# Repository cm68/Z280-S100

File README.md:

# Z280 S-100 CPU Card

A 16-bit **Zilog Z280** CPU card for the **IEEE-696 S-100** backplane. All the
glue logic lives in two **Atmel ATF1508AS** CPLDs, and the entire schematic +
PCB are Python-generated (`gen_kicad.py`, `gen_pcb.py`).

## Key characteristics

| | |
|---|---|
| CPU | Zilog Z280, 16-bit, Z-BUS @ **12 MHz** |
| Bus | IEEE-696 S-100, 100-pin edge connector |
| Glue logic | 2× Atmel ATF1508AS (128 macrocells each) |
| RAM | **2 MB** SRAM — 4× IS61C5128AS-25 (512K×8, 25 ns), word-addressed as 1M×16 |
| Boot ROM | **64 KB** EEPROM — 2× AT28C256 (32K×8) |
| Console | RS-232 via MAX232, 2×5 IDC header (J7) |
| Data-bus drive | 74F245 — meets the IEEE-696 24 mA sink spec |

The board is a **bus master** by default: it drives address, status, control and
data onto the backplane. The CPLDs split the work cleanly:

- **Control CPLD** (`U4`, `z280-s100-ctl.pld`) — "the decider". Arbitration, the
  master-bridge state machine, local-memory control, and the pre-qualified
  steering terms (`MST_RD/MST_WR/SLV_RD/SLV_WR`, `XFR16`, `SPLIT`, `SLAVE`).
- **Data CPLD** (`U5`, `z280-s100-ad.pld`) — "everything that moves bits". The
  AD0-15 byte mux to the S-100 DO/DI lanes, the burst address counter, and the
  byte lane.

Address decode is external: a 74F138 (SRAM window) + two 74F521 comparators
(flash window, slave window). The A3–A15 address lines are latched out through
two 74F573s, and the 16-bit data bus runs through two 74F245 transceivers.

## Memory map (24-bit address space)

| Range | Size | Decode | Device |
|---|---|---|---|
| `000000`–`1FFFFF` | 2 MB | 74F138 (`SRAM_WIN`) / 74F521 (`SLAVE_WIN`) | SRAM — board + temporary-master access |
| `F00000`–`F0FFFF` | 64 KB | 74F521, A23:A16 = `F0` | Boot EEPROM |

The boot EEPROM pair is word-addressed (flash A_n = byte A_{n+1}), so the two
parts span 64 KB. They are *not* socket-interchangeable with 27C256s (pin 27 is
`WE#` here, not A14).

## Local-memory DMA (temporary-master access)

Another S-100 master can take the bus and read/write this card's local SRAM
directly — DMA-style, without the Z280:

1. The temporary master (TMA) asserts **HOLD**; the control CPLD forwards the
   request to the Z280 (`Z_BUSREQ`) and waits for `Z_BUSACK`.
2. With `Z_BUSACK` low the board is a **slave**
   (`SLAVE = !Z_BUSACK # SLAVE_ONLY`): the address/status/control 74F245s
   reverse direction, the data 74F245s float (`S100_DODSB`), and the 74F573
   address latches float their outputs.
3. The TMA reaches this card's RAM through the **slave window** — a
   74F521 comparator (`SLAVE_WIN`, hardwired to `000000`–`1FFFFF`) that maps
   the TMA's address space onto the local SRAM.

The **SLAVE_ONLY** strap (J11) forces this state permanently, turning the card
into a plain memory-only card for bring-up and debug.

## Burst mode

The Z280's memory burst mode (consecutive accesses without re-presenting the
address) is handled in the data CPLD:

- a **2-bit burst address counter** (A1/A2) increments during a burst;
- the **byte lane** (A0) is derived from the low-address bit and the 16→8
  **SPLIT** flag, so byte and word cycles share one data path;
- **16-bit transfers** are detected from WORD and the S-100 **SIXTN**
  (16-bit-acknowledge) line: `SPLIT16 = WORD & !SIXTN`.

`SIXTN` is open-collector (wired-OR) and pulled up via R4, like the ready lines.

## Clock options

Two 24 MHz time-base footprints are laid out; populate exactly **one**:

- **Y1** — parallel-resonant crystal (HC49) across `XTALI`/`XTALO`, or
- **Y2** — a DIP-can oscillator (DIP-8 or DIP-14) driving `XTALI`.

The Z280 auto-detects the source: a crystal enables the on-chip oscillator, while
an external clock into `XTALI` bypasses it (leave `XTALO` open). There is no
strap for this. Either way the CPU clock is half the XTAL1 frequency, so
**24 MHz → 12 MHz processor clock**.

## Configuration jumpers

### J10 — BTI register straps (3×8 header)

The Z280 samples AD0-7 on the rising edge of reset to load its **Bus Timing &
Initialization (BTI)** register — the wait-state field, clock divider,
bootstrap and multiprocessor bits. J10 is a 3×8 header, one row per bit: the
centre pin selects +5V (logic 1) or GND (logic 0); a 74HCT244 (U21) drives the
value onto AD0-7 for the whole reset window.

**Default = `0b10001110`** (AD7…AD0): direct clock, no bootstrap, no
multiprocessor, **3 wait states**, bus clock = CPU clock.

### J11 — SLAVE_ONLY

2-pin header. **Open (default)** = normal bus master. **Jumper to +5V** =
permanent slave (memory-only card). R3 (1 kΩ) holds the line low when open.

### SLAVE_WIN — temporary-master window

A 74F521 comparator hardwired to `000000`–`1FFFFF` (the same 2 MB window as
SRAM) selects where a temporary master sees this card's SRAM. Not user-
configurable on this rev.

### FLASH_WE — boot-ROM write protection

The 28C256 `WE#` line is normally driven by the control CPLD (in-system EEPROM
programming). Strap it to +5V to hard-write-protect the boot ROM.

## Repository layout

| Path | Purpose |
|---|---|
| `gen_kicad.py` | Generates the schematic (`.kicad_sch`, `.kicad_sym`, `NOTES.md`) |
| `gen_pcb.py` | Generates the board (`.kicad_pcb`) — components, nets, power planes |
| `sync_pcb.py` | Reads hand-tweaked PCB placement back into `gen_pcb.py` |
| `z280-s100-ctl.pld` | Control CPLD (U4) logic — arbitration, FSM, memory control |
| `z280-s100-ad.pld` | Data CPLD (U5) logic — byte mux, burst counter, byte lane |
| `z280-s100-*.jed` | Compiled CPLD fuse maps (fit with WinCUPL + ProChip, flashed over JTAG) |

CPLDs are flashed over the JTAG header (TDI/TMS/TCK/TDO on pins 14/23/62/71).

## License

[CERN Open Hardware Licence Version 2 - Permissive](LICENSE) (CERN-OHL-P-2.0).
Fork, modify and build it freely — just don't claim you designed it: keep the
attribution.

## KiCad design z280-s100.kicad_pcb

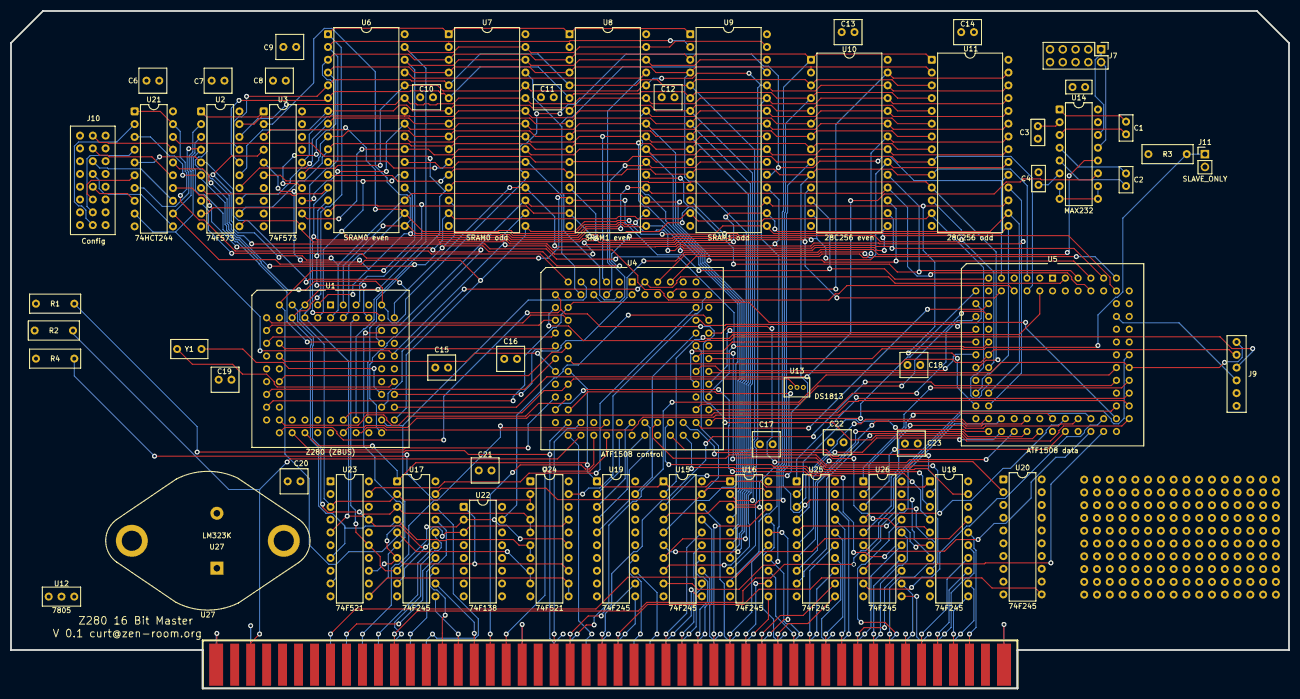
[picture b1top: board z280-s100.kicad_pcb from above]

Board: 4 copper layers, 254.0 x 134.6 mm, 60 parts (0 on the bottom side), 202 nets.

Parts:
C1, C2, C3, C4, C5: 0.1uF; C_Disc_D5.0mm_W2.5mm_P2.50mm
C6, C7, C8, C9, C10, C11, C12, C13, C14, C15, C16, C17, C18, C19, C20, C21, C22, C23: 0.1uF; CAP-2
J7: Serial (2x5); PinHeader_2x05_P2.54mm_Vertical
J9: JTAG; HDR-6
J10: Config; HDR-3x8
J11: SLAVE_ONLY; PinHeader_1x02_P2.54mm_Vertical
R1: 1k pRDY; HDR-2
R2: 1k XRDY; HDR-2
R3: 1k SLAVE_ONLY; HDR-2
R4: 1k SIXTN; HDR-2
U1: Z280 (ZBUS); PLCC-68_THT-Socket
U2, U3: 74F573; DIP-20_W7.62mm
U4: ATF1508 control; PLCC-84_THT-Socket
U5: ATF1508 data; PLCC-84_THT-Socket
U6: SRAM0 even; DIP-32_W15.24mm
U7: SRAM0 odd; DIP-32_W15.24mm
U8: SRAM1 even; DIP-32_W15.24mm
U9: SRAM1 odd; DIP-32_W15.24mm
U10: 28C256 even; DIP-28_W15.24mm
U11: 28C256 odd; DIP-28_W15.24mm
U12: 7805; HDR-3
U13: DS1813; HDR-3
U14: MAX232; DIP-16_W7.62mm
U15, U16, U17, U18, U19, U20, U25, U26: 74F245; DIP-20_W7.62mm
U21: 74HCT244; DIP-20_W7.62mm
U22: 74F138; DIP-16_W7.62mm
U23, U24: 74F521; DIP-20_W7.62mm
U27: LM323K; TO-3
V 0.1 curt@zen-room.org: Z280 16 Bit Master; S100_MALE
Y1: 24 MHz crystal; HDR-2

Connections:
+5V: C5.1, C6.1, C7.1, C8.1, C9.1, C10.1, C11.1, C12.1, C13.1, C14.1, C15.1, C16.1, C17.1, C18.1, C19.1, C20.1, C21.1, C22.1, C23.1, J9.6, J10.1, J10.4, J10.7, J10.10, J10.13, J10.16, J10.19, J10.22, J11.2, R1.1, R2.1, R4.1, U1.18, U1.19, U1.34, U2.20, U3.20, U4.1, U4.2, U4.3, U4.13, U4.26, U4.38, U4.43, U4.53, U4.66, U4.78, U4.84, U5.1, U5.2, U5.3, U5.13, U5.26, U5.38, U5.43, U5.53, U5.66, U5.78, U5.84, U6.32, U7.32, U8.32, U9.32, U10.28, U11.28, U12.3, U13.3, U14.16, U15.20, U16.20, U17.20, U18.20, U19.20, U20.1, U20.20, U21.20, U22.6, U22.16, U23.12, U23.14, U23.16, U23.18, U23.20, U24.20, U25.20, U26.20, U27.2
+8V: U12.1, U27.1, V 0.1 curt@zen-room.org.1, V 0.1 curt@zen-room.org.51
A0: U5.4, U15.2
A1: U5.5, U6.12, U7.12, U8.12, U9.12, U10.10, U11.10, U15.3
A2: U5.6, U6.11, U7.11, U8.11, U9.11, U10.9, U11.9, U15.4
A3: U2.12, U6.10, U7.10, U8.10, U9.10, U10.8, U11.8, U15.5
A4: U2.13, U6.9, U7.9, U8.9, U9.9, U10.7, U11.7, U15.6
A5: U2.14, U6.8, U7.8, U8.8, U9.8, U10.6, U11.6, U15.7
A6: U2.15, U6.7, U7.7, U8.7, U9.7, U10.5, U11.5, U15.8
A7: U2.16, U6.6, U7.6, U8.6, U9.6, U10.4, U11.4, U15.9
A8: U2.17, U6.5, U7.5, U8.5, U9.5, U10.3, U11.3, U16.2
A9: U2.18, U6.27, U7.27, U8.27, U9.27, U10.25, U11.25, U16.3
A10: U2.19, U6.26, U7.26, U8.26, U9.26, U10.24, U11.24, U16.4
A11: U3.12, U6.23, U7.23, U8.23, U9.23, U10.21, U11.21, U16.5
A12: U3.13, U6.25, U7.25, U8.25, U9.25, U10.23, U11.23, U16.6
A13: U3.14, U6.4, U7.4, U8.4, U9.4, U10.2, U11.2, U16.7
A14: U3.15, U6.28, U7.28, U8.28, U9.28, U10.26, U11.26, U16.8
A15: U3.16, U6.3, U7.3, U8.3, U9.3, U10.1, U11.1, U16.9
A16: U1.5, U6.31, U7.31, U8.31, U9.31, U17.2, U23.3, U24.2, U24.3
A17: U1.6, U6.2, U7.2, U8.2, U9.2, U17.3, U23.5, U24.4, U24.5
A18: U1.8, U6.1, U7.1, U8.1, U9.1, U17.4, U23.7, U24.6, U24.7
A19: U1.9, U6.30, U7.30, U8.30, U9.30, U17.5, U23.9, U24.8, U24.9
A20: U1.45, U4.9, U17.6, U23.11, U24.11, U24.12
A21: U1.59, U17.7, U22.1, U23.13, U24.13
A22: U1.66, U17.8, U22.2, U23.15, U24.15
A23: U1.7, U17.9, U22.3, U23.17, U24.17
AD0: U1.40, U5.24, U7.13, U9.13, U11.11, U21.18
AD1: U1.42, U5.25, U7.14, U9.14, U11.12, U21.16
AD2: U1.43, U5.27, U7.15, U9.15, U11.13, U21.14
AD3: U1.44, U2.2, U5.28, U7.17, U9.17, U11.15, U21.12
AD4: U1.54, U2.3, U5.29, U7.18, U9.18, U11.16, U21.9
AD5: U1.57, U2.4, U5.30, U7.19, U9.19, U11.17, U21.7
AD6: U1.60, U2.5, U5.31, U7.20, U9.20, U11.18, U21.5
AD7: U1.61, U2.6, U5.9, U7.21, U9.21, U11.19, U21.3
AD8: U1.62, U2.7, U5.10, U6.13, U8.13, U10.11
AD9: U1.64, U2.8, U5.11, U6.14, U8.14, U10.12
AD10: U1.65, U2.9, U5.75, U6.15, U8.15, U10.13
AD11: U1.67, U3.2, U5.76, U6.17, U8.17, U10.15
AD12: U1.68, U3.3, U5.77, U6.18, U8.18, U10.16
AD13: U1.2, U3.4, U5.79, U6.19, U8.19, U10.17
AD14: U1.3, U3.5, U5.80, U6.20, U8.20, U10.18
AD15: U1.4, U3.6, U5.81, U6.21, U8.21, U10.19
BTI_AD0: J10.2, U21.2
BTI_AD1: J10.5, U21.4
BTI_AD2: J10.8, U21.6
BTI_AD3: J10.11, U21.8
BTI_AD4: J10.14, U21.11
BTI_AD5: J10.17, U21.13
BTI_AD6: J10.20, U21.15
BTI_AD7: J10.23, U21.17
CFG_OE: U4.11, U21.1, U21.19
CPLD_DI0: U5.44, U26.2
CPLD_DI1: U5.45, U26.3
CPLD_DI2: U5.46, U26.4
CPLD_DI3: U5.48, U26.5
CPLD_DI4: U5.49, U26.6
CPLD_DI5: U5.50, U26.7
CPLD_DI6: U5.51, U26.8
CPLD_DI7: U5.52, U26.9
CPLD_DO0: U5.33, U25.2
CPLD_DO1: U5.34, U25.3
CPLD_DO2: U5.35, U25.4
CPLD_DO3: U5.36, U25.5
CPLD_DO4: U5.37, U25.6
CPLD_DO5: U5.39, U25.7
CPLD_DO6: U5.40, U25.8
CPLD_DO7: U5.41, U25.9
CPLD_pDBIN: U4.45, U19.4
CPLD_pHLDA: U4.48, U20.2
CPLD_pSTVAL: U4.44, U19.3
CPLD_pSYNC: U4.41, U19.2
CPLD_pWR: U4.46, U19.5
CPLD_sHLTA: U4.31, U18.7
CPLD_sINP: U4.51, U18.4
CPLD_sINTA: U4.30, U18.6
CPLD_sMEMR: U4.49, U18.2
CPLD_sOUT: U4.52, U18.5
CPLD_sWO: U4.50, U18.3
CPLD_sXTRQ: U4.65, U18.8
DI_DIR: U5.60, U26.1
DO_DIR: U5.58, U25.1
FLASH_CE: U4.81, U10.20, U11.20
FLASH_OE: U4.79, U10.22, U11.22
FLASH_WE: U4.80, U10.27, U11.27
FLASH_WIN: U4.73, U23.19
GND: C3.2, C4.2, C5.2, C6.2, C7.2, C8.2, C9.2, C10.2, C11.2, C12.2, C13.2, C14.2, C15.2, C16.2, C17.2, C18.2, C19.2, C20.2, C21.2, C22.2, C23.2, J7.3, J7.4, J7.5, J7.6, J7.7, J7.8, J7.9, J7.10, J9.5, J10.3, J10.6, J10.9, J10.12, J10.15, J10.18, J10.21, J10.24, R3.1, U1.1, U1.35, U1.51, U1.53, U2.10, U3.7, U3.8, U3.9, U3.10, U4.7, U4.19, U4.32, U4.42, U4.47, U4.59, U4.72, U4.82, U5.7, U5.19, U5.32, U5.42, U5.47, U5.59, U5.72, U5.82, U6.16, U7.16, U8.16, U9.16, U10.14, U11.14, U12.2, U13.1, U14.15, U15.10, U16.10, U17.10, U18.10, U19.10, U20.3, U20.4, U20.5, U20.6, U20.7, U20.8, U20.9, U20.10, U20.19, U21.10, U22.4, U22.5, U22.8, U23.1, U23.2, U23.4, U23.6, U23.8, U23.10, U24.1, U24.10, U24.14, U24.16, U24.18, U25.10, U25.19, U26.10, U26.19, U27.3, V 0.1 curt@zen-room.org.20, V 0.1 curt@zen-room.org.50, V 0.1 curt@zen-room.org.53, V 0.1 curt@zen-room.org.70, V 0.1 curt@zen-room.org.100
JTAG_CHAIN: U4.71, U5.14
JTAG_TCK: J9.1, U4.62, U5.62
JTAG_TDI: J9.3, U4.14
JTAG_TDO: J9.4, U5.71
JTAG_TMS: J9.2, U4.23, U5.23
LA0: U4.63, U5.22
LATCH_LE: U2.11, U3.11, U5.8
MAX_C1M: C1.2, U14.3
MAX_C1P: C1.1, U14.1
MAX_C2M: C2.2, U14.5
MAX_C2P: C2.1, U14.4
MAX_RS232_RX: J7.2, U14.13
MAX_RS232_TX: J7.1, U14.14
MAX_VM: C4.1, U14.6
MAX_VP: C3.1, U14.2
MEM_CE0: U4.10, U6.22, U7.22
MEM_CE1: U4.8, U8.22, U9.22
MEM_OE: U4.5, U6.24, U7.24, U8.24, U9.24
MEM_WE_H: U4.4, U7.29, U9.29
MEM_WE_L: U4.6, U6.29, U8.29
MST_RD: U4.54, U5.12
MST_WR: U4.55, U5.15
NC: U14.7, U14.8, U14.9, U14.10
S100_A0: U15.11, V 0.1 curt@zen-room.org.79
S100_A1: U15.12, V 0.1 curt@zen-room.org.80
S100_A2: U15.13, V 0.1 curt@zen-room.org.81
S100_A3: U15.14, V 0.1 curt@zen-room.org.31
S100_A4: U15.15, V 0.1 curt@zen-room.org.30
S100_A5: U15.16, V 0.1 curt@zen-room.org.29
S100_A6: U15.17, V 0.1 curt@zen-room.org.82
S100_A7: U15.18, V 0.1 curt@zen-room.org.83
S100_A8: U16.11, V 0.1 curt@zen-room.org.84
S100_A9: U16.12, V 0.1 curt@zen-room.org.34
S100_A10: U16.13, V 0.1 curt@zen-room.org.37
S100_A11: U16.14, V 0.1 curt@zen-room.org.87
S100_A12: U16.15, V 0.1 curt@zen-room.org.33
S100_A13: U16.16, V 0.1 curt@zen-room.org.85
S100_A14: U16.17, V 0.1 curt@zen-room.org.86
S100_A15: U16.18, V 0.1 curt@zen-room.org.32
S100_A16: U17.11, V 0.1 curt@zen-room.org.16
S100_A17: U17.12, V 0.1 curt@zen-room.org.17
S100_A18: U17.13, V 0.1 curt@zen-room.org.15
S100_A19: U17.14, V 0.1 curt@zen-room.org.59
S100_A20: U17.15, V 0.1 curt@zen-room.org.61
S100_A21: U17.16, V 0.1 curt@zen-room.org.62
S100_A22: U17.17, V 0.1 curt@zen-room.org.63
S100_A23: U17.18, V 0.1 curt@zen-room.org.64
S100_ADSB: U4.36, V 0.1 curt@zen-room.org.22
S100_A_OE: U4.67, U15.19, U16.19, U17.19
S100_CDSB: U4.39, V 0.1 curt@zen-room.org.19
S100_C_OE: U4.69, U19.19
S100_DI0: U26.11, V 0.1 curt@zen-room.org.95
S100_DI1: U26.12, V 0.1 curt@zen-room.org.94
S100_DI2: U26.13, V 0.1 curt@zen-room.org.41
S100_DI3: U26.14, V 0.1 curt@zen-room.org.42
S100_DI4: U26.15, V 0.1 curt@zen-room.org.91
S100_DI5: U26.16, V 0.1 curt@zen-room.org.92
S100_DI6: U26.17, V 0.1 curt@zen-room.org.93
S100_DI7: U26.18, V 0.1 curt@zen-room.org.43
S100_DO0: U25.11, V 0.1 curt@zen-room.org.36
S100_DO1: U25.12, V 0.1 curt@zen-room.org.35
S100_DO2: U25.13, V 0.1 curt@zen-room.org.88
S100_DO3: U25.14, V 0.1 curt@zen-room.org.89
S100_DO4: U25.15, V 0.1 curt@zen-room.org.38
S100_DO5: U25.16, V 0.1 curt@zen-room.org.39
S100_DO6: U25.17, V 0.1 curt@zen-room.org.40
S100_DO7: U25.18, V 0.1 curt@zen-room.org.90
S100_DODSB: U5.61, V 0.1 curt@zen-room.org.23
S100_HOLD: U4.33, V 0.1 curt@zen-room.org.74
S100_INT: U5.63, V 0.1 curt@zen-room.org.73
S100_NMI: U5.64, V 0.1 curt@zen-room.org.12
S100_SDSB: U4.37, V 0.1 curt@zen-room.org.18
S100_SIXTN: R4.2, U4.40, V 0.1 curt@zen-room.org.60
S100_S_OE: U4.68, U18.19
S100_XRDY: R2.2, U4.35, V 0.1 curt@zen-room.org.3
S100_pDBIN: U19.13, V 0.1 curt@zen-room.org.78
S100_pHLDA: U20.11, V 0.1 curt@zen-room.org.26
S100_pRDY: R1.2, U4.34, V 0.1 curt@zen-room.org.72
S100_pSTVAL: U19.12, V 0.1 curt@zen-room.org.25
S100_pSYNC: U19.11, V 0.1 curt@zen-room.org.76
S100_pWR: U19.14, V 0.1 curt@zen-room.org.77
S100_sHLTA: U18.16, V 0.1 curt@zen-room.org.48
S100_sINP: U18.13, V 0.1 curt@zen-room.org.46
S100_sINTA: U18.15, V 0.1 curt@zen-room.org.96
S100_sMEMR: U18.11, V 0.1 curt@zen-room.org.47
S100_sOUT: U18.14, V 0.1 curt@zen-room.org.45
S100_sWO: U18.12, V 0.1 curt@zen-room.org.97
S100_sXTRQ: U18.17, V 0.1 curt@zen-room.org.58
SLAVE: U2.1, U3.1, U4.58, U5.21
SLAVE_ONLY: J11.1, R3.2, U4.64
SLAVE_WIN: U4.74, U24.19
SLV_RD: U4.56, U5.16
SLV_WR: U4.57, U5.17
SPLIT: U4.61, U5.20
SRAM_WIN: U4.70, U22.15
XFR16: U4.60, U5.18
XTALI: U1.50, Y1.1
XTALO: U1.49, Y1.2
Z_AS: U1.27, U4.12, U5.54
Z_BUSACK: U1.31, U4.25, U15.1, U16.1, U17.1, U18.1, U19.1
Z_BUSREQ: U1.28, U4.29
Z_BW: U1.10, U4.17
Z_CLK: U1.47, U4.83, U5.83
Z_DS: U1.24, U4.15, U5.55
Z_IE: U1.17, U4.24
Z_INT: U1.37, U5.56
Z_NMI: U1.39, U5.57
Z_RESET: U1.38, U4.27, U13.2
Z_RW: U1.12, U4.16
Z_RXD: U1.48, U14.12
Z_ST0: U1.14, U4.18
Z_ST1: U1.15, U4.20
Z_ST2: U1.21, U4.21
Z_ST3: U1.22, U4.22
Z_TXD: U1.46, U14.11
Z_WAIT: U1.29, U4.28

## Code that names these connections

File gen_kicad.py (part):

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    inst.append(emit_symbol_instance("Crystal", "Y1", 294.64, 127.0,
                 {"1":"XTALI","2":"XTALO"}))
    # DIP oscillator (Y2), an alternative time base to the crystal Y1. Both drive
    # XTALI; only one is stuffed at build time. Pins 4/7 (GND) and 5/8 (OUT) are
    # the DIP-8 / DIP-14 positions and are shorted by the netlist.
    inst.append(emit_symbol_instance("Oscillator", "Y2", 231.14, 232.41,
                 {"4":"GND","7":"GND","5":"XTALI","8":"XTALI","14":"+5V"}))
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  divider). One row per bit: col 0 = +5V (HIGH), col 1 = signal (BTI_ADn),
  col 2 = GND (LOW). Shunt col1→+5V = 1, col1→GND = 0.
- The 74HCT244 (U21) tri-state driver presents that value on AD0-7 during the
  reset-config window: both /OE (pins 1, 19) tie to CFG_OE from the control
  CPLD. The CPLD asserts WAIT >=4 clocks before reset rises and holds it 15
  clocks after (datasheet p.541/545; 6 is the floor, the extra is free since the
  CPU sits on WAIT), and CFG_OE tracks that same dwell, so AD0-7 stays driven
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  the DIRs are gated by S100_DODSB so a temporary master can float our drivers.

## Address latch (74F573, U2/U3)
- A3-A15 moved out of CPLD B into two 74F573s to free pins for DO_DIR/DI_DIR.
  LE = LATCH_LE (= ~AS: transparent while AS is low, holds on the rising edge);
  /OE = SLAVE so the latch floats its Q outputs when a TMA drives address inward.
  A0 (byte lane) and A1/A2 (burst counter) stay in the CPLD — they need the
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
